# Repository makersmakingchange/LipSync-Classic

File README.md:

# LipSync Classic

> [!IMPORTANT]
**As of 2024-Feb-08, this version of the LipSync is now obsolete and has been replaced by the [LipSync 4](https://github.com/makersmakingchange/LipSync).** 

The LipSync Classic is an assistive technology device that allows quadriplegics and other people with limited hand function to use touchscreen mobile devices, tablets, and computers by manipulation of a mouth-operated joystick with integrated sip and puff controls. This is an Open-Source Hardware project, so the Lipsync can be made at the community level for less than $300.

## Compatibility 

 <table style="width:100%">
  <tr>
    <th>Operating Systems</th>
    <th>Version</th>
    <th>Release</th>
    <th>Additional Information</th>
  <tr>
    <td>iOS</td>
    <td>13.1</td>
    <td>September 19,2019</td>
    <td>Compatible with iPhone 7 and newer versions (Requires USB to Lightning or USB to USB-C Adapter)</td>
  </tr>
  <tr>
    <td>Windows</td>
    <td>XP,7,10</td>
    <td>2001</td>
    <td>Compatible with Windows XP and newer versions</td>
  </tr>
  <tr>
    <td>Android</td>
    <td>4-9</td>
    <td>Released 2013</td>
    <td>Compatible with Android 4 and newer versions (Requires USB On-The-Go)</td>
  </tr>
  <tr>
    <td>MacOS</td>
    <td>10</td>
    <td>Released 2000</td>
    <td>Compatible with Mac OS X 10.0 and newer versions</td>
  </tr>
  </table> 

## Download

 <table style="width:100%">
  <tr>
    <th>Resource</th>
    <th>Version</th>
    <th>Format</th>
    <th>Link</th>
  </tr>
    <tr>
    <td>LipSync All</td>
    <td>3.0</td>
    <td>ZIP</td>
    <td><a href="https://github.com/makersmakingchange/LipSync/archive/refs/heads/main.zip">LipSync.zip</a></td>
  </tr>
  <tr>
    <td>LipSync Assembly Guide</td>
    <td>1.6</td>
    <td>PDF</td>
    <td><a href="https://github.com/makersmakingchange/LipSync/blob/main/Documentation/LipSync_Assembly_Guide.pdf">LipSync_Assembly_Guide.pdf</a></td>
  </tr>
  <tr>
    <td>LipSync Startup Guide</td>
    <td>1.8</td>
    <td>PDF</td>
    <td><a href="https://github.com/makersmakingchange/LipSync/blob/main/Documentation/LipSync_Startup_Guide.pdf">LipSync_Startup_Guide.pdf</a></td>
  </tr>
  <tr>
    <td>LipSync User Guide</td>
    <td>1.3</td>
    <td>PDF</td>
    <td><a href="https://github.com/makersmakingchange/LipSync/blob/main/Documentation/LipSync_User_Guide.pdf">LipSync_User_Guide.pdf</a></td>
  </tr>
  <tr>
     <td>LipSync Mounting Guide</td>
     <td>1.0</td>
     <td>PDF</td>
     <td><a href="https://github.com/makersmakingchange/LipSync/blob/main/Documentation/LipSync_Mounting_Guide.pdf">LipSync_Mounting_Guide.pdf</a></td>
  </tr>
  <tr>
    <td>LipSync BOM (XLSX)</td>
    <td>September 1, 2021</td>
    <td>XLSX</td>
    <td><a href="https://github.com/makersmakingchange/LipSync/blob/main/Documentation/LipSync_BOM.xlsx">LipSync_BOM.xlsx</a></td>
  </tr>
  <tr>
    <td>LipSync BOM (CSV)</td>
    <td>September 1, 2021</td>
    <td>CSV</td>
    <td><a href="https://github.com/makersmakingchange/LipSync/blob/main/Documentation/LipSync_BOM.csv">LipSync_BOM.csv</a></td>
  </tr>
  <tr>
    <td>LipSync Firmware</td>
    <td>3.0</td>
    <td>INO</td>
    <td><a href="https://raw.githubusercontent.com/makersmakingchange/LipSync/main/Software/LipSync_Firmware/LipSync_Firmware.ino">LipSync_Firmware.ino</a></td>
  </tr>
  <tr>
    <td>LipSync Interface Board Layout</td>
    <td>2.71</td>
    <td>BRD</td>
    <td><a href="https://raw.githubusercontent.com/makersmakingchange/LipSync/main/Hardware/PCB_design/Eagle/LipSync_Interface_Board/LipSync_Interface_Board.brd">LipSync_Interface_Board.brd</a></td>
  </tr>
  <tr>
    <td>LipSync Interface Board Schematic</td>
    <td>2.71</td>
    <td>SCH</td>
    <td><a href="https://raw.githubusercontent.com/makersmakingchange/LipSync/main/Hardware/PCB_design/Eagle/LipSync_Interface_Board/LipSync_Interface_Board.sch">LipSync_Interface_Board.sch</a></td>
  </tr>
  <tr>
    <td>JLCPCB LipSync Interface Board Gerber</td>
    <td>2.71</td>
    <td>ZIP</td>
    <td><a href="https://github.com/makersmakingchange/LipSync/raw/main/Hardware/PCB_design/Gerber/LipSync_Interface_Board/JLCPCB_LipSync_Interface_Board.zip">JLCPCB_LipSync_Interface_Board.zip</a></td>
  </tr>
  <tr>
    <td>OSHPark LipSync Interface Board Gerber</td>
    <td>2.71</td>
    <td>ZIP</td>
    <td><a href="https://github.com/makersmakingchange/LipSync/raw/main/Hardware/PCB_design/Gerber/LipSync_Interface_Board/OSHPark_LipSync_Interface_Board.zip">OSHPark_LipSync_Interface_Board.zip</a></td>
  </tr>
  <tr>
    <td>PCBWay LipSync Interface Board Gerber</td>
    <td>2.71</td>
    <td>ZIP</td>
    <td><a href="https://github.com/makersmakingchange/LipSync/raw/main/Hardware/PCB_design/Gerber/LipSync_Interface_Board/PCBWay_LipSync_Interface_Board.zip">PCBWay_LipSync_Interface_Board.zip</a></td>
  </tr>
  <tr>
    <td>Seeed Fusion LipSync Interface Board Gerber</td>
    <td>2.71</td>
    <td>ZIP</td>
    <td><a href="https://github.com/makersmakingchange/LipSync/raw/main/Hardware/PCB_design/Gerber/LipSync_Interface_Board/Seeed_Fusion_LipSync_Interface_Board.zip">Seeed_Fusion_LipSync_Interface_Board.zip</a></td>
  </tr>
  <tr>
    <td rowspan="9">Housing_design</td>
    <td rowspan="9">3.0</td>
    <td rowspan="9">STL</td>
    <td><a href="https://github.com/makersmakingchange/LipSync/blob/main/Hardware/Housing_design/LipSync_Button.stl">LipSync_Button.STL</a></td>
  </tr>
  <tr>
  <td><a href="https://github.com/makersmakingchange/LipSync/blob/main/Hardware/Housing_design/LipSync_Front_Housing.STL">LipSync_Front_Housing.STL</a></td>
  </tr>
  <tr>
	<td><a href="https://github.com/makersmakingchange/LipSync/blob/main/Hardware/Housing_design/LipSync_Joystick_Base.STL">LipSync_Joystick_Base.STL</a></td>
</tr>
<tr>
  <td><a href="https://github.com/makersmakingchange/LipSync/blob/main/Hardware/Housing_design/LipSync_Joystick_Front.STL">LipSync_Joystick_Front.STL</a></td>
</tr>
<tr>
  <td><a href="https://github.com/makersmakingchange/LipSync/blob/main/Hardware/Housing_design/LipSync_Joystick_Rocker.STL">LipSync_Joystick_Rocker.STL</a></td>
</tr>
<tr>
    <td><a href="https://github.com/makersmakingchange/LipSync/blob/main/Hardware/Housing_design/Optional/LipSync_Joystick_Jig.STL">LipSync_Joystick_Jig.STL</a></td>
</tr>
<tr>
  <td><a href="https://github.com/makersmakingchange/LipSync/blob/main/Hardware/Housing_design/LipSync_Rear_Housing.STL">LipSync_Rear_Housing.STL</a></td>
</tr>
<tr>
  <td><a href="https://github.com/makersmakingchange/LipSync/blob/main/Hardware/Housing_design/3D_Print_Settings.txt">3D_Print_Settings.txt</a></td>
</tr>
</table> 

## Resources

<table style="width:100%">
  <tr>
    <th>Resource</th>
    <th>Link</th>
  </tr>
  <tr>
    <td>LipSync Firmware and Calibration Video</td>
    <td><a href="https://www.youtube.com/watch?v=RnpA24WH0Qk">Video</a></td>
  <tr>
    <td>LipSync Joystick Calibration Video</td>
    <td><a href="https://www.youtube.com/watch?v=Daf-54y6SBg">Video</a></td>
  </tr>
    <tr>
    <td>LipSync Build Video</td>
    <td><a href="https://www.youtube.com/watch?v=lBXpbkp5DW4&list=PLhoPg9bDvBR4CSFRfNbQ87ALnfaHOyM3C">Video</a></td>
  </tr>
</table> 

## License
Copyright (c) 2016-2024 Neil Squire / Makers Making Change.

This repository describes Open Hardware:
 - Everything needed or used to design, make, test, or prepare the LipSync Classic is licensed under the [CERN 2.0 Weakly Reciprocal license (CERN-OHL-W v2) or later](https://cern.ch/cern-ohl ) .
 - All software is under the [GNU General Public License v3.0 (GPL-3.0)](https://www.gnu.org/licenses/gpl.html).
 - Accompanying material such as instruction manuals, videos, and other copyrightable works that are useful but not necessary to design, make, test, or prepare the LipSync are published under a [Creative Commons Attribution-ShareAlike 4.0 license (CC BY-SA 4.0)](https://creativecommons.org/licenses/by-sa/4.0/) .

You may redistribute and modify this documentation and make products using it under the terms of the [CERN-OHL-W v2](https://cern.ch/cern-ohl).
This documentation is distributed WITHOUT ANY EXPRESS OR IMPLIED WARRANTY, INCLUDING OF MERCHANTABILITY, SATISFACTORY QUALITY AND FITNESS FOR A PARTICULAR PURPOSE.
Please see the CERN-OHL-W v2 for applicable conditions.

Source Location: https://github.com/makersmakingchange/LipSync-Classic

## Attribution

The LipSync was designed by Neil Squire Society / Makers Making Change. The initial development of a 3D printable LipSync was supported by the Google Impact Challenge: Disabilities grant from Google.org. Further development was supported through the Government of Canada's Innovation Science and Economic Development Assistive Technology Program. These and other funders have also enabled Neil Squire / Makers Making Change to deploy numerous LipSyncs to users at reduced cost.

The LipSync firmware utilizes the Arduino development platform, an open-source electronics platform based on easy-to-use hardware and software. Arduino is developed and maintained by the Arduino community, and the project wouldn't be possible without their contributions. Arduino is a registered trademark of Arduino AG. For more information about Arduino and to contribute to the community, visit the official Arduino website at www.arduino.cc.

### Contributors

Numerous Neil Squire staff, users, and volunteers have contribued to the development of the LipSync. 

 - Derrick Andrews
 - Ivan Gourlay
 - Jake McIvor
 - Kristina Mok
 - Milad Hajihassan

----

<!-- ABOUT MMC START -->
## About Makers Making Change

Makers Making Change is a program of [Neil Squire](https://www.neilsquire.ca/), a Canadian non-profit that uses technology, knowledge, and passion to empower people with disabilities.

Makers Making Change leverages the capacity of community based Makers, Disability Professionals and Volunteers to develop and deliver affordable Open Source Assistive Technologies.

 - Website: [www.MakersMakingChange.com](https://www.makersmakingchange.com/)
 - GitHub: [makersmakingchange](https://github.com/makersmakingchange)
 - Bluesky: [@makersmakingchange.bsky.social](https://bsky.app/profile/makersmakingchange.bsky.social)
 - Instagram: [@makersmakingchange](https://www.instagram.com/makersmakingchange)
 - Facebook: [makersmakechange](https://www.facebook.com/makersmakechange)
 - LinkedIn: [Neil Squire Society](https://www.linkedin.com/company/neil-squire-society/)
 - Thingiverse: [makersmakingchange](https://www.thingiverse.com/makersmakingchange/about)
 - Printables: [MakersMakingChange](https://www.printables.com/@MakersMakingChange)

### Contact Us
For technical questions, to get involved, or to share your experience we encourage you to [visit our website](https://www.makersmakingchange.com/) or [contact us](https://www.makersmakingchange.com/s/contact).
<!-- ABOUT MMC END -->

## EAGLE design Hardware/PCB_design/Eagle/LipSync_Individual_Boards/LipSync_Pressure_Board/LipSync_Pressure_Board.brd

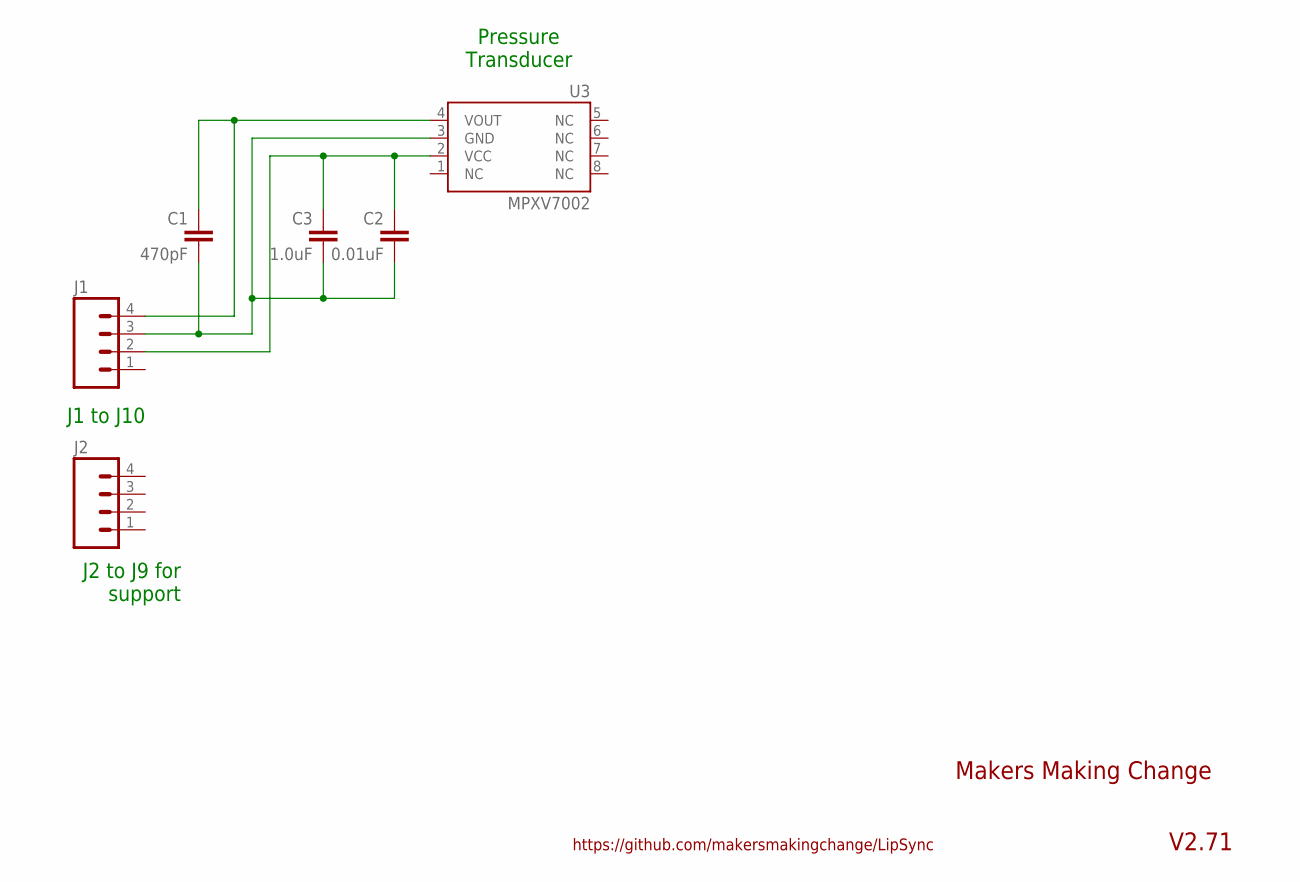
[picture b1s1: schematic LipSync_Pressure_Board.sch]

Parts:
C1: 470pF; CAP-PTH-SMALLEZ
C2: 0.01uF; CAP-PTH-SMALLEZ
C3: 1.0uF; CAP-PTH-SMALLEZ
J1, J2: M04PTH; 1X04
U3: MPXV7002; SOP8

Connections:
GND2: C1.2, C2.2, C3.2, J1.3, U3.3 (GND)
unnamed: C1.1, J1.4, U3.4 (VOUT)
unnamed: C2.1, C3.1, J1.2, U3.2 (VCC)

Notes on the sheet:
J2 to J9 for support
J1 to J10
Pressure Transducer
Makers Making Change
V2.71
https://github.com/makersmakingchange/LipSync

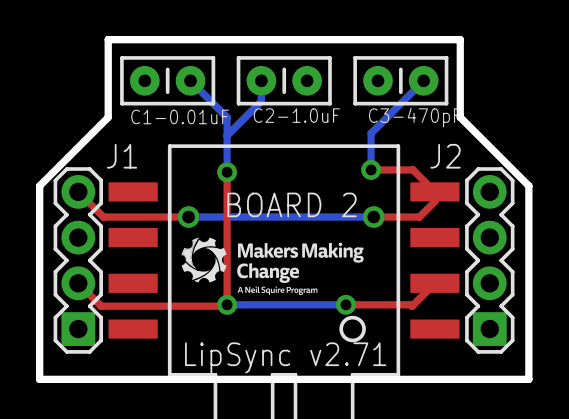
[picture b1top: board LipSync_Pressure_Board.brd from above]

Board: 2 copper layers, 27.2 x 18.9 mm, 6 parts (0 on the bottom side), 3 nets.

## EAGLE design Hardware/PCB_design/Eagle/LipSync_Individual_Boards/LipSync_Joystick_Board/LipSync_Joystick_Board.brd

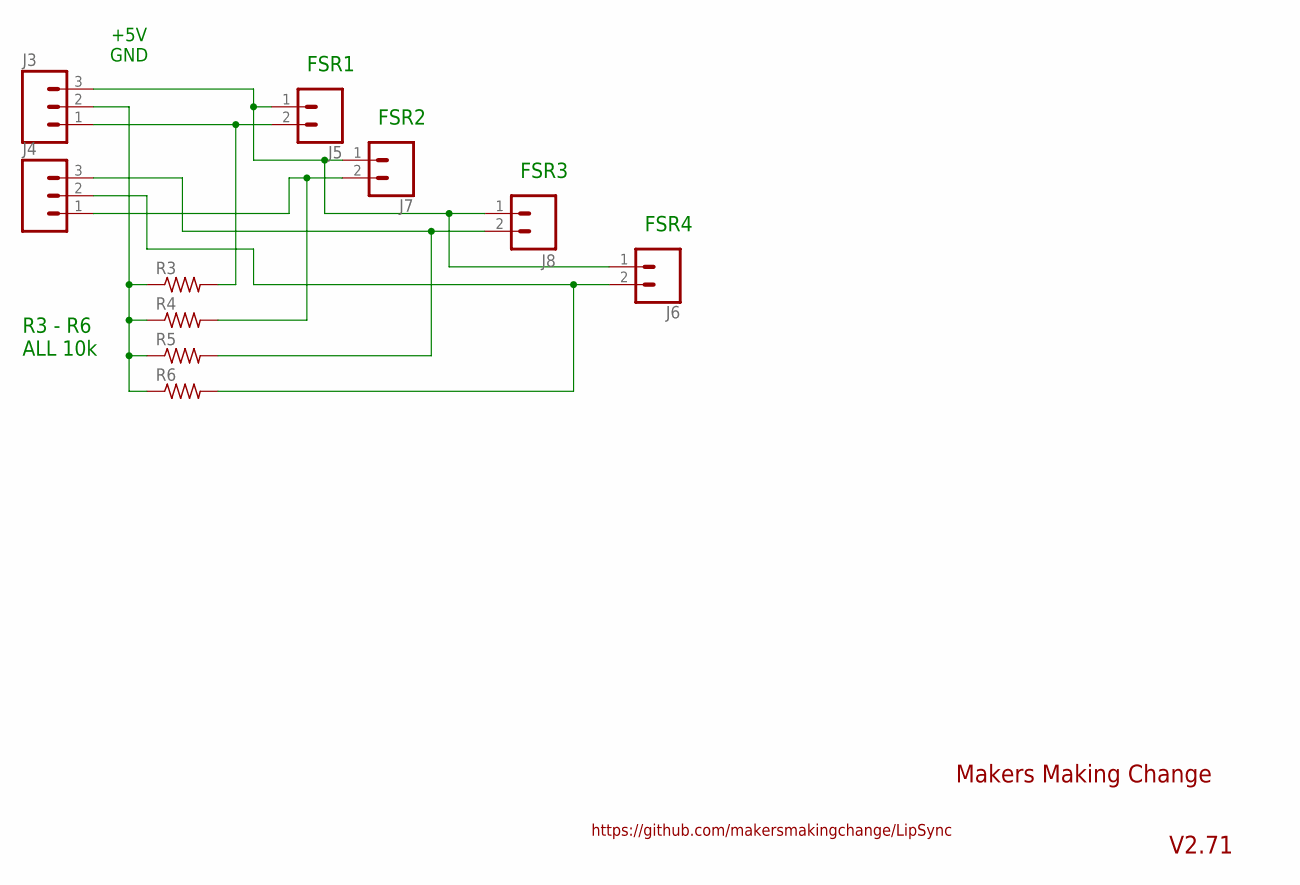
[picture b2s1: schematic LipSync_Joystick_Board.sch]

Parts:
J3, J4: M03LOCK; 1X03_LOCK
J5, J6, J7: CONN_02PTH3; 1X02_LONGPADS
J8: M02PTH3; 1X02_LONGPADS@1
R3, R4, R5, R6: R-US_0204/5; 0204/5

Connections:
GND3: J3.2, R3.1, R4.1, R5.1, R6.1
unnamed: J3.3, J5.1, J6.1, J7.1, J8.1
unnamed: J3.1, J5.2, R3.2
unnamed: J4.1, J7.2, R4.2
unnamed: J4.3, J8.2, R5.2
unnamed: J4.2, J6.2, R6.2

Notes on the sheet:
+5V GND
R3 - R6 ALL 10k
FSR1
FSR2
FSR3
FSR4
Makers Making Change
V2.71
https://github.com/makersmakingchange/LipSync

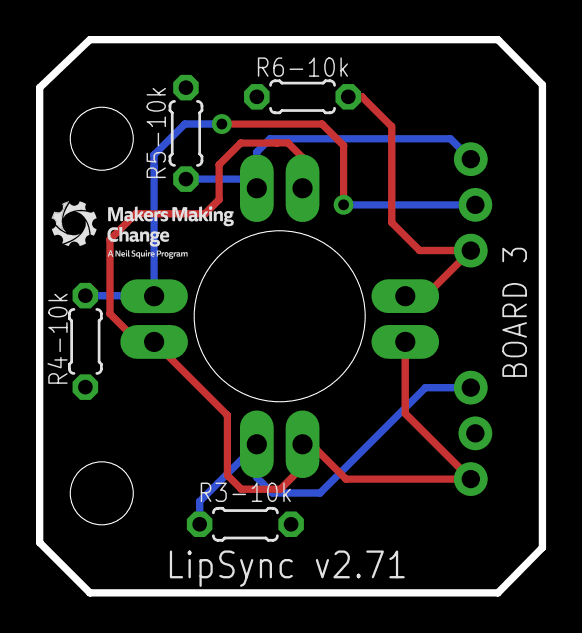
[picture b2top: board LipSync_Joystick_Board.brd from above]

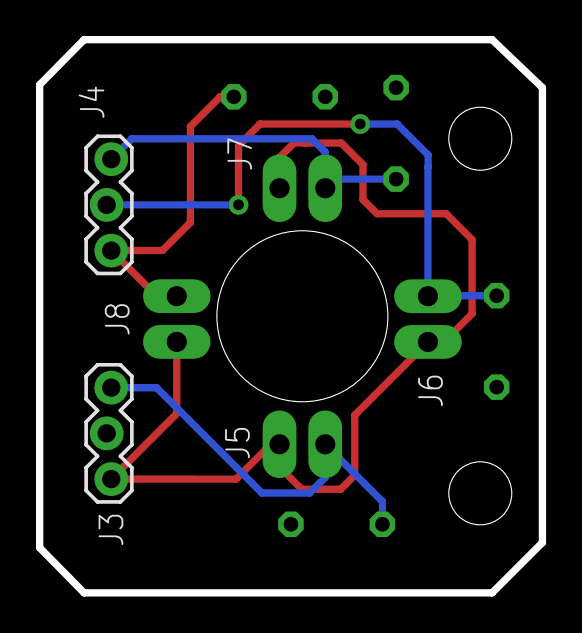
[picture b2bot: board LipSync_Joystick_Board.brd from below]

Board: 2 copper layers, 27.9 x 30.7 mm, 10 parts (6 on the bottom side), 6 nets.

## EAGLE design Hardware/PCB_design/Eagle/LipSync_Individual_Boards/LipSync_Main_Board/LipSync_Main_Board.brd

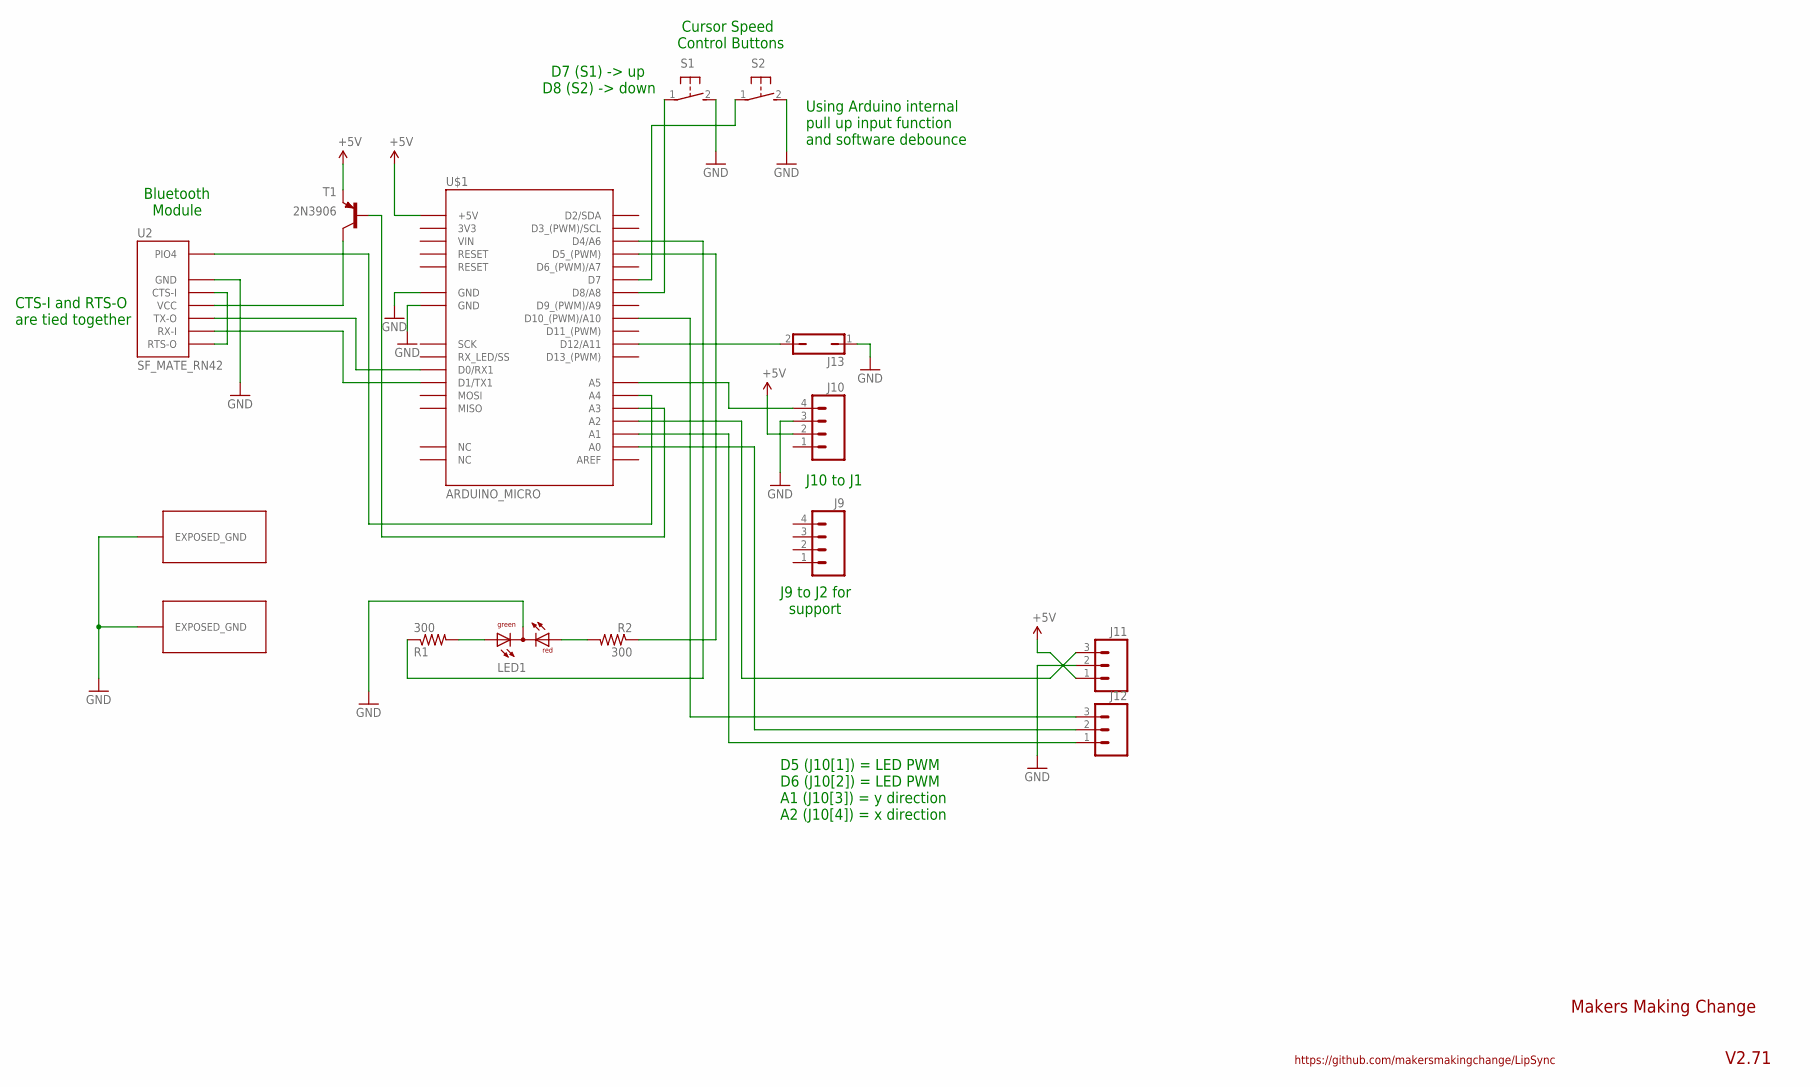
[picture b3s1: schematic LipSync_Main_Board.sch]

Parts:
J9, J10: M04PTH; 1X04
J11, J12: M03LOCK; 1X03_LOCK
J13: JP1Q; JP1
LED1: DUOLED-RG-C; DUOLED-C-5MM
R1, R2: 300; AXIAL-0.3
S1, S2: 31-XXB3F-31XX-CUSTOM; B3F-31XX-CUSTOM
T1: 2N3906; TO92-EBC
U2: SF_MATE_RN42; BLUE_MATE_RN42_HEADER_FOOTPRINT
U$1: ARDUINO_MICRO; ARDUINO_MICRO_HEADER_FOOTPRINT
U$2, U$3: EXPOSED_GND

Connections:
3V3: U$1.3V3
GND: J10.3, J11.2, J13.1, LED1.C, S1.2 (S), S2.2 (S), U2.GND, U$1.GND, U$1.GND@1 (GND), U$2.GND1, U$3.GND1
unnamed: U2.PIO4, U$1.A4
unnamed: T1.C, U2.VCC
unnamed: U2.TX-O, U$1.RX1 (D0/RX1)
unnamed: U2.RX-I, U$1.TX1 (D1/TX1)
unnamed: J12.2, U$1.A0
unnamed: J12.1, U$1.A1
unnamed: U2.CTS-I, U2.RTS-O
unnamed: J12.3, U$1.D10 (D10_(PWM)/A10)
unnamed: J10.4, U$1.A5
unnamed: LED1.AX (AG), R1.P$2 (2)
unnamed: LED1.AR, R2.P$2 (2)
unnamed: S1.1, U$1.D8 (D8/A8)
unnamed: S2.1, U$1.D7
unnamed: R1.P$1 (1), U$1.D4 (D4/A6)
unnamed: R2.P$1 (1), U$1.D5 (D5_(PWM))
unnamed: T1.B, U$1.A3
unnamed: J11.3, U$1.A2
unnamed: J13.2, U$1.D12 (D12/A11)
VCC: J10.2, J11.1, T1.E, U$1.5V (+5V)

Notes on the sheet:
J9 to J2 for support
D5 (J10[1]) = LED PWM D6 (J10[2]) = LED PWM A1 (J10[3]) = y direction A2 (J10[4]) = x direction
CTS-I and RTS-O are tied together
J10 to J1
Cursor Speed Control Buttons
D7 (S1) -> up D8 (S2) -> down
Bluetooth Module
Using Arduino internal pull up input function and software debounce
Makers Making Change
V2.71
https://github.com/makersmakingchange/LipSync

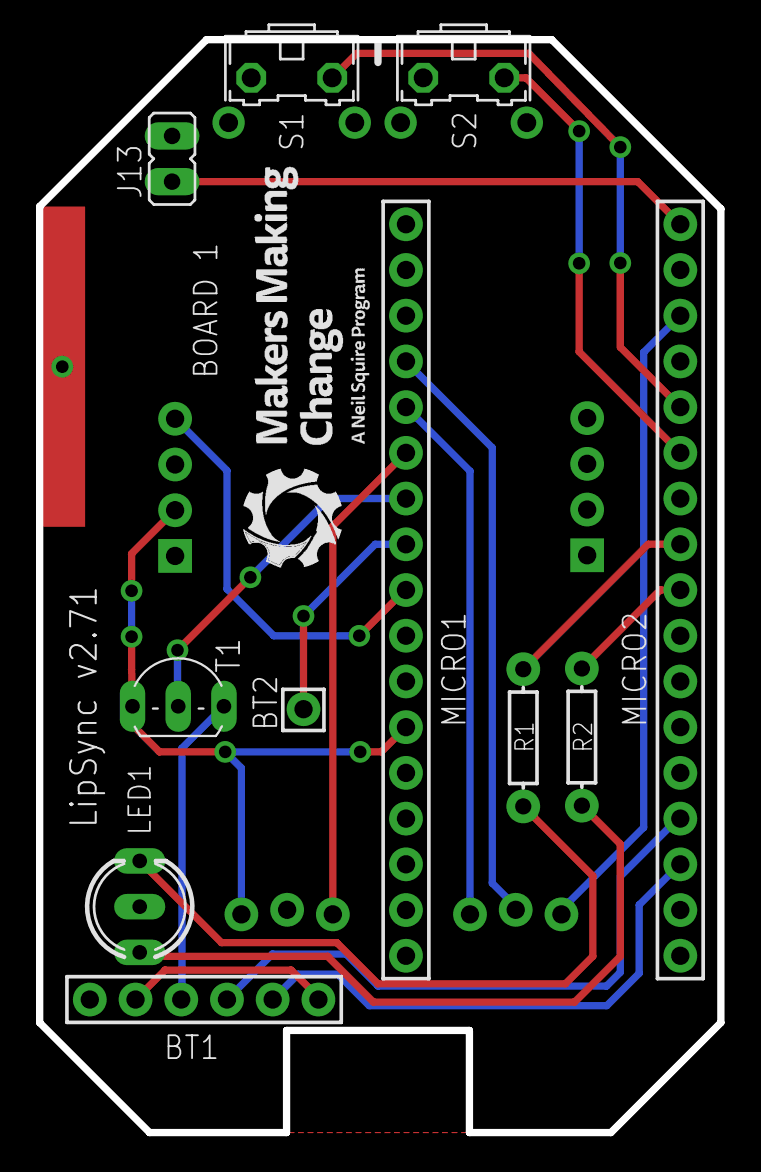
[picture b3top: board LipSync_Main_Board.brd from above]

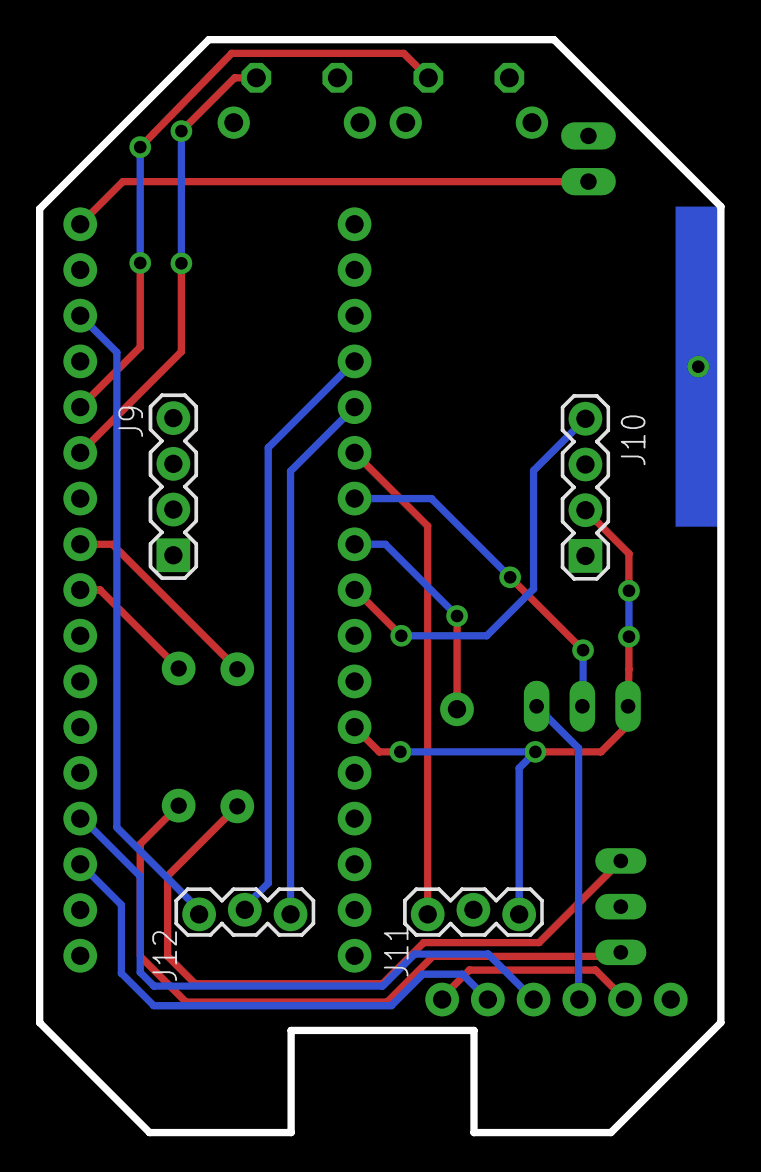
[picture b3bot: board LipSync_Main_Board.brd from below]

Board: 2 copper layers, 37.8 x 60.7 mm, 15 parts (5 on the bottom side), 20 nets.

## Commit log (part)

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2017-02-06 Created hardware directory for STL files
2017-02-10 Updated README.md
    Added Contact Us and Licensing to README.md
2017-02-17 Changed license
    It's recommend against using a CC license on software and hardware.
    https://creativecommons.org
2017-02-18 Added Eagle PCB layout files version 2.5
2017-02-18 Added LipSync FSR Arduino code version 2.4 (Jan 28th ) FSR_Fast_Load
2017-02-18 Changed directory naming convention
2017-02-18 Added blog link to README file
    Added blog link to README file
2017-02-25 Changed naming conversion for STL files
2017-02-25 Changed naming conversion for Arduino code
2017-02-28 Updated Lipsync firmware Version 2.5 ( 27 Feb 2017 )
2017-03-04 Updated STL Files
2017-03-10 LipSync Components in CSV format
2017-03-10 Updated list of LipSync Components
2017-03-11 Update README.md
    Added Hackaday page link.
2017-03-11 Added Instructions manual for assembling a LipSync
2017-03-11 Added startup Guide for first using and operating a LipSync
2017-03-12 Update README.md
    Add LipSync Logo to Readme file.
2017-04-06 Updated parts list
2017-05-10 This is just a test
2017-05-10 This is the end of the test
2017-05-14 Updated LipSync Firmware Version 2.6 May 9
2017-06-13 Updated Assembly Manual 1.41 and Startup guide.
2017-06-13 Updated Assembly Manual 1.41
2017-06-28 Updated STL files to V2.2d
2017-07-24 Corrected mesh quality issues for Front Housing
2017-10-02 Added Mounting Document
2017-10-26 Updated BOM file ( October 25,2017 )
2017-10-26 Updated readme file
2017-11-01 Updated Manual
2017-12-13 Updated Manual (v.1.4.5.1)
2018-01-05 Updated PCB eagle files to version 2.7
2018-01-10 Updated Startup Guide (v1.23)
2018-03-02 Updated BOM file (March 2, 2018)
2018-03-12 Updated BOM file (March 12, 2018)
2018-05-08 Assembly Manual
2018-06-19 Updated BOM file (June 19, 2018)
2018-07-03 Updated BOM file (July 3, 2018)
2018-10-12 Create LipSync_Firmware_Joystick_Only.ino
    The LipSync will only have joystick feature after uploading the code.
2018-10-12 minor changes
2018-11-13 Added the pdf version of Lipsync boards and schematics
2018-12-03 Updated Startup Guide (v1.3)
2019-06-13 Updated Startup Guide (June 13, 2019)
2019-07-09 LipSync_Startup_Guide.pdf
    Updated Startup Guide (v1.4)
2019-08-13 Update BOM (2019-Aug-13)
    Updated link for Lee Springs
2019-09-17 Updated BOM file
2019-10-01 Update to V2.3
    - The shell is slightly longer and the rear portion is slightly wider to accommodate a greater range of USB cables. The cut-out near the mounting hole is also larger and longer to prevent the threade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
    - A recess has been added to the bottom to provide a less conspicuous location to apply any labelling.
    - The rear portion of the shell is larger and has greater surface area which should help mitigate any bed adhesion issues.
    - The cylindrical portions that house the springs have been lengthened and a catch was added that should retain the springs once they are pressed in. These changes should help m
2019-10-01 Added PCB files Version 2.71 with updated MMC Logo.
2019-10-01 Updated PCB version number in readme file.
2019-10-22 Updated the firmware to 2.7.
2020-03-09 Added the updated LipSync Manual, LipSync User Guide, LipSync Setup Guide, and LipSync BOM File.
2020-04-15 Added PCB board gerber files.
2020-04-15 Updated readme file
    Added the links to PCB board gerber files.
2020-05-08 PCB Fabricaiton Manual
2020-06-25 Firmware with added serial command for communication with LipSync App.
2020-07-06 Corrected Settings commands
2020-07-07 Increased debug mode time delay.
2020-07-30 Added Startup and User Guide MD files.
2020-07-30 Updated LipSync_User_Guide.md
2020-07-30 Uploaded .docx working files
2020-07-31 Moved word files to sub directory
2020-08-01 Added UpSideDown Firmware
2020-08-10 Corrected changeTolerance variable type
2020-08-10 Updated the command document
2020-08-10 Added change tolerance for each FSR
2020-08-19 Corrected variable names to make it easier to understand the code
2020-11-25 Resolved EEPROM Debug and raw Mode status bug.
2020-12-07 Updated to v1.6
2021-02-03 Delete LipSync_Rear_Housing.stl
    Remove ascii version to avoid confusion
2021-02-08 Added cleaning instructions and troubleshooting tips
2021-04-02 Initial rotation angle code
    Initial commit of rotation angle code
2021-04-02 Create LipSync_Command_List.docx
    Add copy of serial interface command list
2021-04-07 Code reorg
    Code cleanup
2021-04-07 Update firmware description
    More inclusive LipSync description
2021-05-07 Default action button mapping added as a constant
2021-05-07 Create LipSync_Common.h
    Create common header file for different LipSync versions.
2021-05-07 Update LipSync_Firmware.ino
    Basic inclusion of common header file.
2021-05-07 Update LipSync_Firmware.ino
    Implement basic scroll for different to rotation angles
2021-05-07 Update LipSync_Firmware.ino
    Change scroll delay from 250ms to CursorDelay
2021-05-07 Update LipSync_Firmware.ino
    Fix scroll direction
2021-05-07 Update LipSync_Firmware.ino
    Minor comment changes.
2021-05-08 Added numeric validation to check the modifier part of input commands
2021-05-11 Remove header file.
2021-05-11 Update LipSync_Firmware.ino
    Remove header file link.
2021-05-12 Updated EEPROM locations to constants defined at the beginning and updated factoryreset function to use functions instead of direct EEPROM read/write
2021-05-12 Update LipSync_Firmware.ino
    Typo fix
2021-05-12 Rename LipSync Joystick Stand to LipSync Joystick Jig
2021-05-12 Update LipSync_Rear_Housing.STL
    - Add light pipe hole for Bluetooth Module
    - Add visual icon to Bluetooth Light Pipe and status indicator
    - Extend USB cable slot to provide more clearance between cable and mounting hardware
    - Add additional cable slot for Switch Input cables.
    - Add fillets to bottom circuit board support to reduce stress concentration and improve printability
2021-05-14 Corrected Serial Settings logic and EEPROM raw mode variable name
2021-05-15 Updated flag API_ENABLED name
2021-05-15 Corrected the API response
2021-05-16 Clarify pushButtonHandler Inputs
    Replace generic variables with more functional indications. Instead of 1 and 2, replaced with up and down to match how the physical switches are referred.
2021-05-17 Add constants for sip and puff delay
    These can function as default values.
2021-05-17 Swap sip and puff to constants; add actionButton[5] to long sip.
2021-05-17 Clean up the API and functions
2021-05-17 Update button mapping
    - Add null action
    - Remap other indices.
2021-05-17 Button Mapping Cleanup
    - Correct EEPROM address duplication.
    - Change naming of defaultButtonMapping to BUTTON_MAPPING to indicate it is a constant coming from code.
    - Add DEFAULT_BUTTON_MAPPING constant to represent MMC defaults.
2021-05-17 Clean up preamble
2021-05-17 Button Mapping
    Expanded documentation, improved readability of code.
2021-05-17 Consolidate cursorModifier functions
    Replace xCursorLow, yCursorLow, yCursorHigh, and xCursorHigh with single function.
2021-05-17 Simplify joystick measurement
    Remove sqrt, change xHighyHighRadius to squared deadband
2021-05-17 Corrected constant names
2021-05-18 Move command list to documentation
2021-05-18 Update LipSync_Command_List.docx
    Update button mapping
    Add examples
2021-05-18 Fix signs in cursor output, add comments
2021-05-18 Need to be floats, not ints to avoid overrun
2021-05-19 Add secondary joystick check to avoid skipChange at held movement
2021-05-19 Converted API check cases and validation process which involved conditional statements to struct. This will allow to add new APIs dynamically.
2021-05-20 Added int array support to api
2021-05-20 Update LipSync_Rear_Housing.STL
    Final update for V3.0 ready for print testing.
    -extended circuit board slot
    -removed label groove
    -update light pipe icons
2021-05-21 Replace xcursor and ycursor global variable with local variable.
2021-05-21 Add comments and descriptive variable names for performCommand function
2021-05-21 Cleanup FSR processing.
2021-05-21 tempParameterArray to inputParameterArray
    + fix typo
2021-05-21 Merged setCursorSpeed, increaseCursorSpeed, decreaseCursorSpeed internal function logic to one function.
2021-05-25 Remove math.h
    Not necessary.
2021-05-25 Swap LED_1 with LED_GREEN and LED_2 with LED_RED
2021-05-25 Add comments and cleanup code.
2021-05-25 Remove unused global variables.
2021-05-25 Cleanup
2021-05-26 Improve naming in cursorModifier; fix mapping
2021-05-26 Add floating point math to avoid cursor overrun
    Added cursorFloat as an intermediate value during initial calculation of cursorOutput using pow(cursorSpeedMax, neutralFactor). Originally, if neutral factor > log(32768)/log(cursorMaxSpeed), this wi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
2021-05-27 New Api response format was added.
2021-05-29 Fixed API bugs
2021-05-29 Cleanup : Changed struct to array
2021-06-01 Updated new API endpoints to use the new serial print out functions
2021-06-01 Corrected Factory reset end point
2021-06-01 Added soft reset
2021-06-02 Added setChangeTolerance
2021-06-02 Added new print function for API
2021-06-02 Updated ascii header
2021-06-02 Cleanup
    - Append g_ to all global variables
    - remove unnecessary global variables (xHigh,xLow,yHigh,yLow, xHighYHigh,..etc)
    - Add readJoystick function to reduce code repetition
    - Add readPressure function to reduce code repetition
2021-06-02 Clean-up xHigh, xLow
2021-06-02 Fix readPressure value
    Should be 1023 instead of 1024.
2021-06-03 Updated print functions and added comments
2021-06-03 Fix integer overrun
2021-06-03 Update version date.
2021-06-04 Updated the command list guide
2021-06-04 Corrected the raw mode and added more comments
2021-07-11 Corrected LipSync API format in the command list document.
2021-07-30 Fixed scroll exit by adding fixed delay.
2021-07-30 Added led clear to scroll function
2021-07-31 Improved scroll exit
2021-07-31 Cleanup sip and puff cursor actions and functions
2021-08-05 Added scroll speed level as user adjustable parameter. Aded secondary scroll
2021-08-05 Rearranged functions for easy remembering and better structure
2021-08-05 Added back the compensation factor which improves diagonal movement
2021-08-06 Added back the poll
2021-08-06 Updated the command list documentation
2021-08-06 Corrected the command list document
2021-08-07 Commented raw mode
2021-08-08 Updated scroll function and made step sizes change based on scroll speed level
2021-08-11 Added variable time delay for each scroll speed level
2021-08-11 Update scroll base movement
2021-08-13 Updated scroll speed level parameters to make it smoother
2021-08-14 Fixed and removed all compiler warnings by making second function definitions
2021-08-14 Added API function definitions comments
2021-08-15 Removed Raw mode and fixed minor bugs
2021-08-15 Updated command list documentation
2021-08-18 Update mounting document name
2021-08-18 Update LipSync_Firmware.ino
    - Add / edit comments
    - Remove unnecessary delays after EEPROM reads
    -
2021-08-18 Optimize and expand unused pin setting
2021-08-18 Update LipSync_Firmware.ino
    Replace 4 separate deadband variables with single constant
2021-08-18 Update LipSync_Firmware.ino
    Remove unnecessary code from ledBlink
2021-08-19 Update LipSync_Firmware.ino
    Separate puff and sip threshold implementation
2021-08-24 Optimized the API
2021-08-25 API format validation was added as commented code
2021-08-26 Fixed API delimiter bug
2021-08-27 Corrected variable name according to our convention
2021-08-31 Update for V3.0
    Update links and information for beta release.
2021-09-01 Move documentation
2021-11-29 Fix Runaway g_pollCounter
2022-06-02 Optimized the code
2022-06-04 Resolved merge conflicts
2022-06-04 Updated lift threshold value
2022-06-09 Corrected link
2022-06-09 Added STL with correct extension
2022-06-16 Updated documents
2022-06-16 Updated readme links
2022-06-16 Updated readme
    Updated links from develop branch to main branch
2022-06-17 Fixed Command mode bug
2022-06-28 Updated Software License
2024-02-02 Update README.md
    Redirect to LipSync 4.0
2025-04-10 Add Update About MMC GitHub Action
2025-04-12 Update About MMC Section
2026-01-05 Change 'master' to 'main' in documentation links
    Updated links in README.md to use 'main' branch instead of 'master'. Added additional contributors.

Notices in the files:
parts and their libraries:
SparkFun-Connectors: Licensing: Creative Commons ShareAlike 4.0 International - https://creativecommons.org/licenses/by-sa/4.0
